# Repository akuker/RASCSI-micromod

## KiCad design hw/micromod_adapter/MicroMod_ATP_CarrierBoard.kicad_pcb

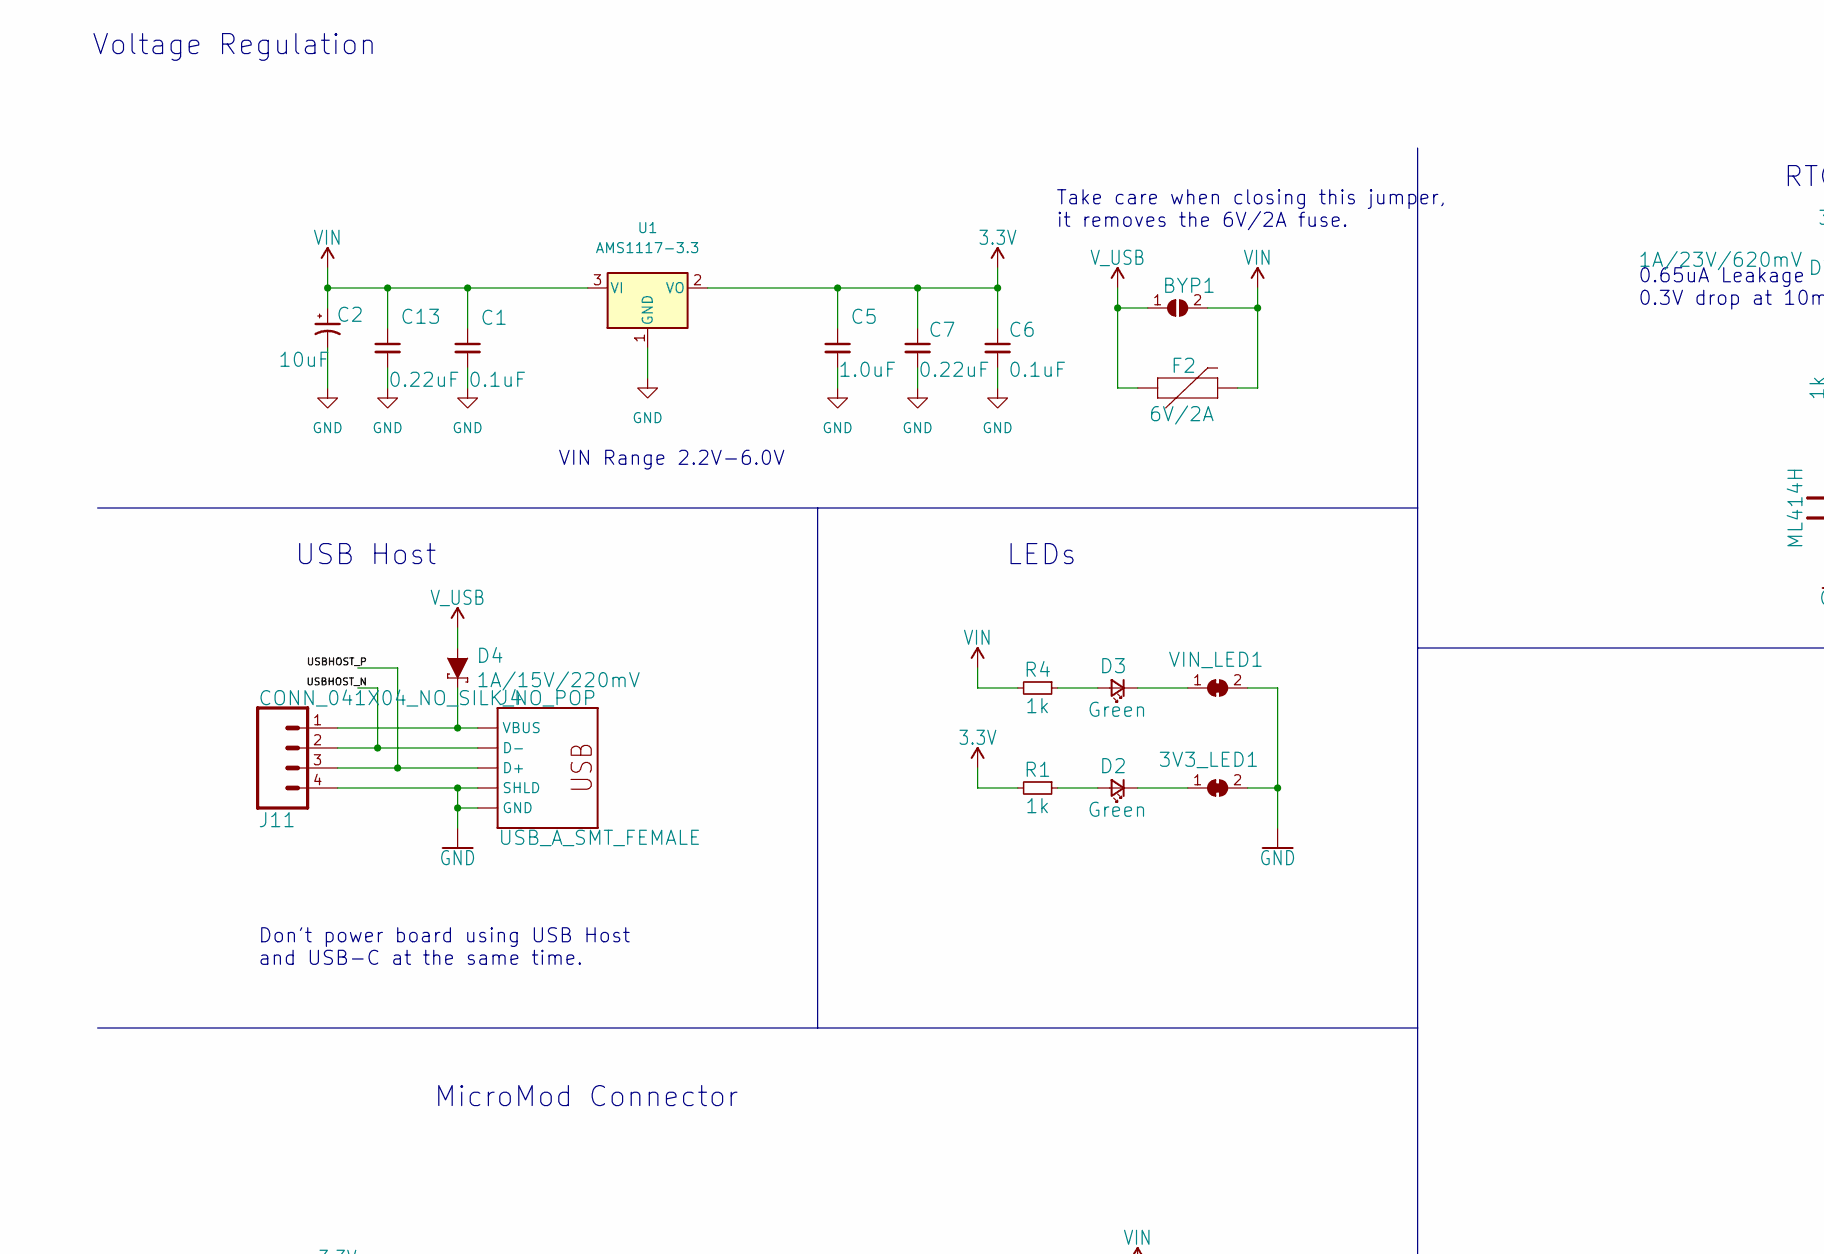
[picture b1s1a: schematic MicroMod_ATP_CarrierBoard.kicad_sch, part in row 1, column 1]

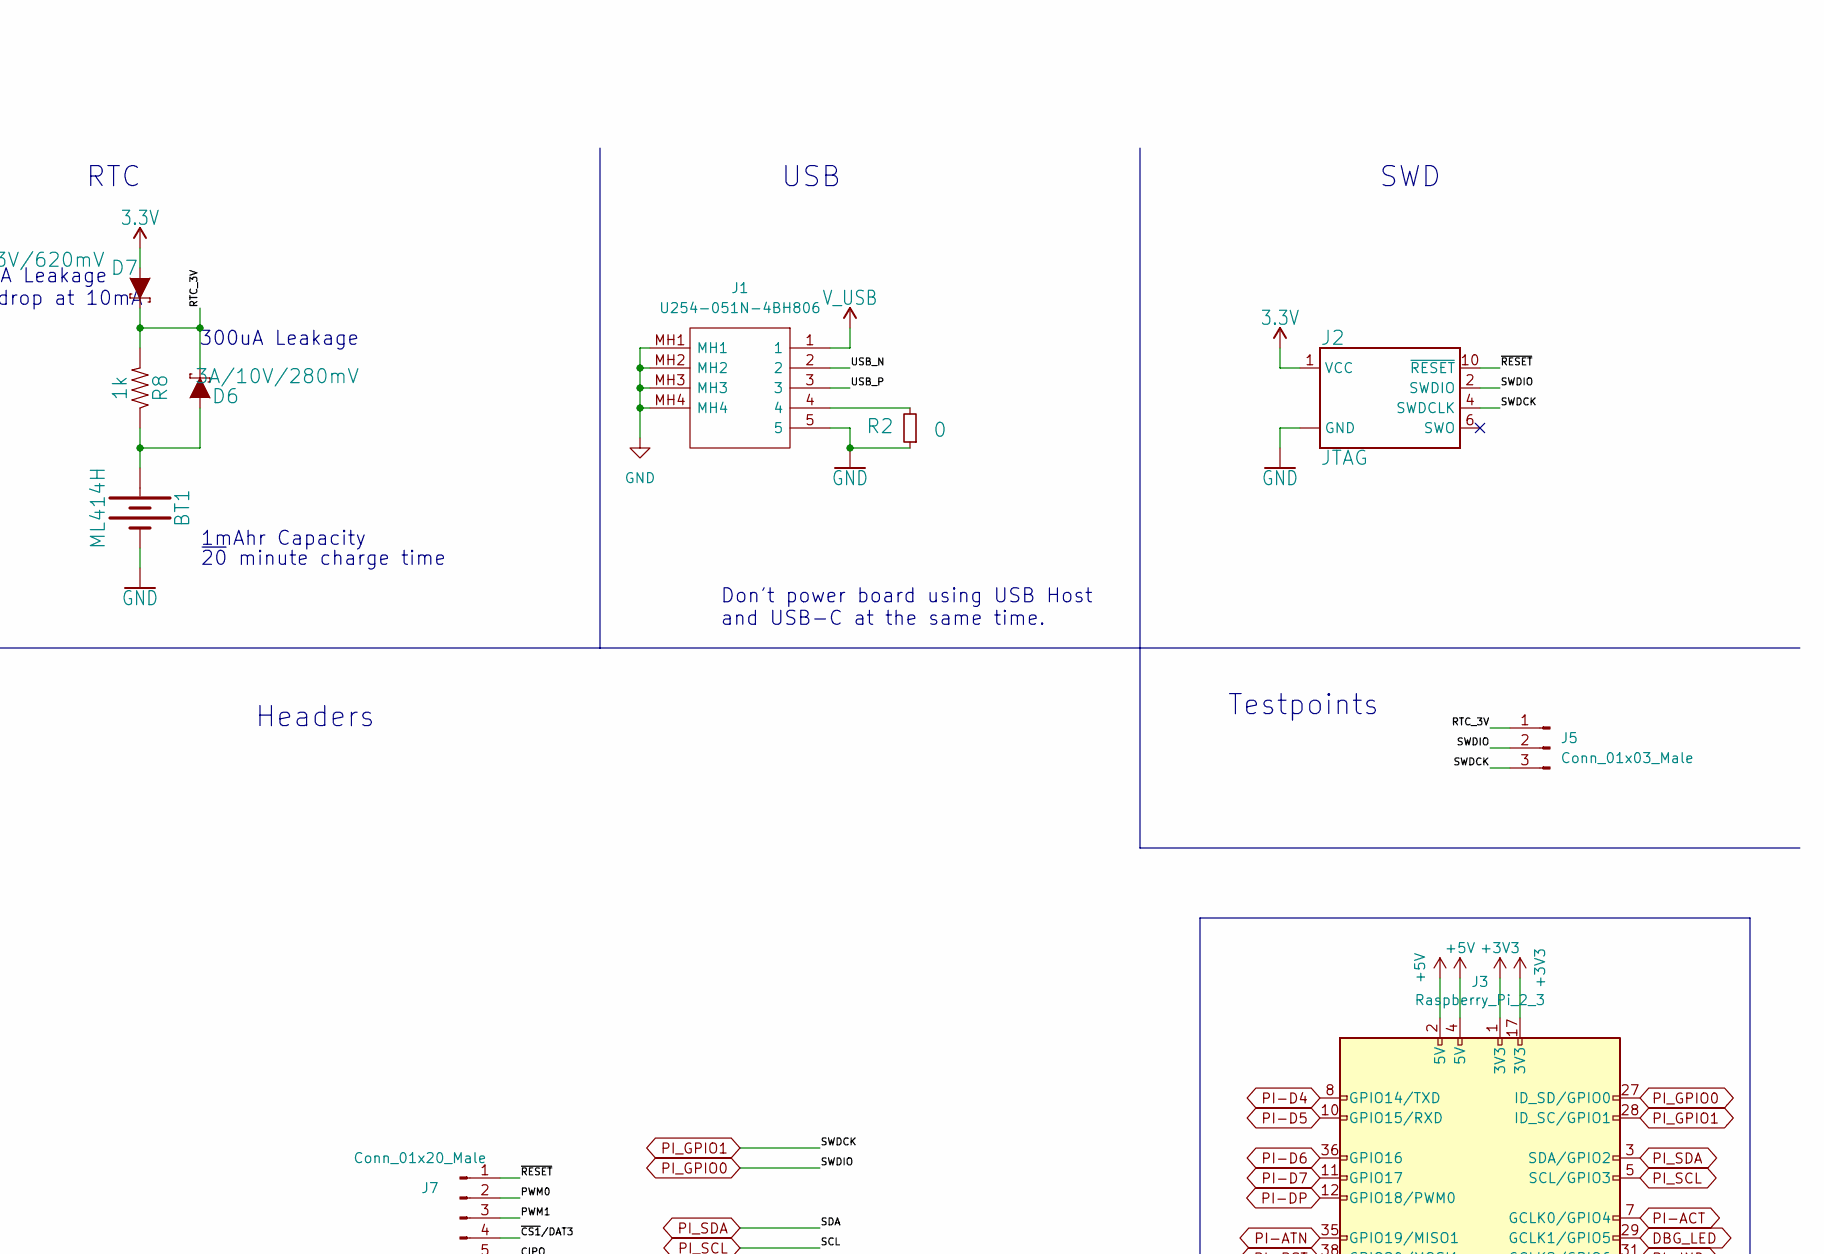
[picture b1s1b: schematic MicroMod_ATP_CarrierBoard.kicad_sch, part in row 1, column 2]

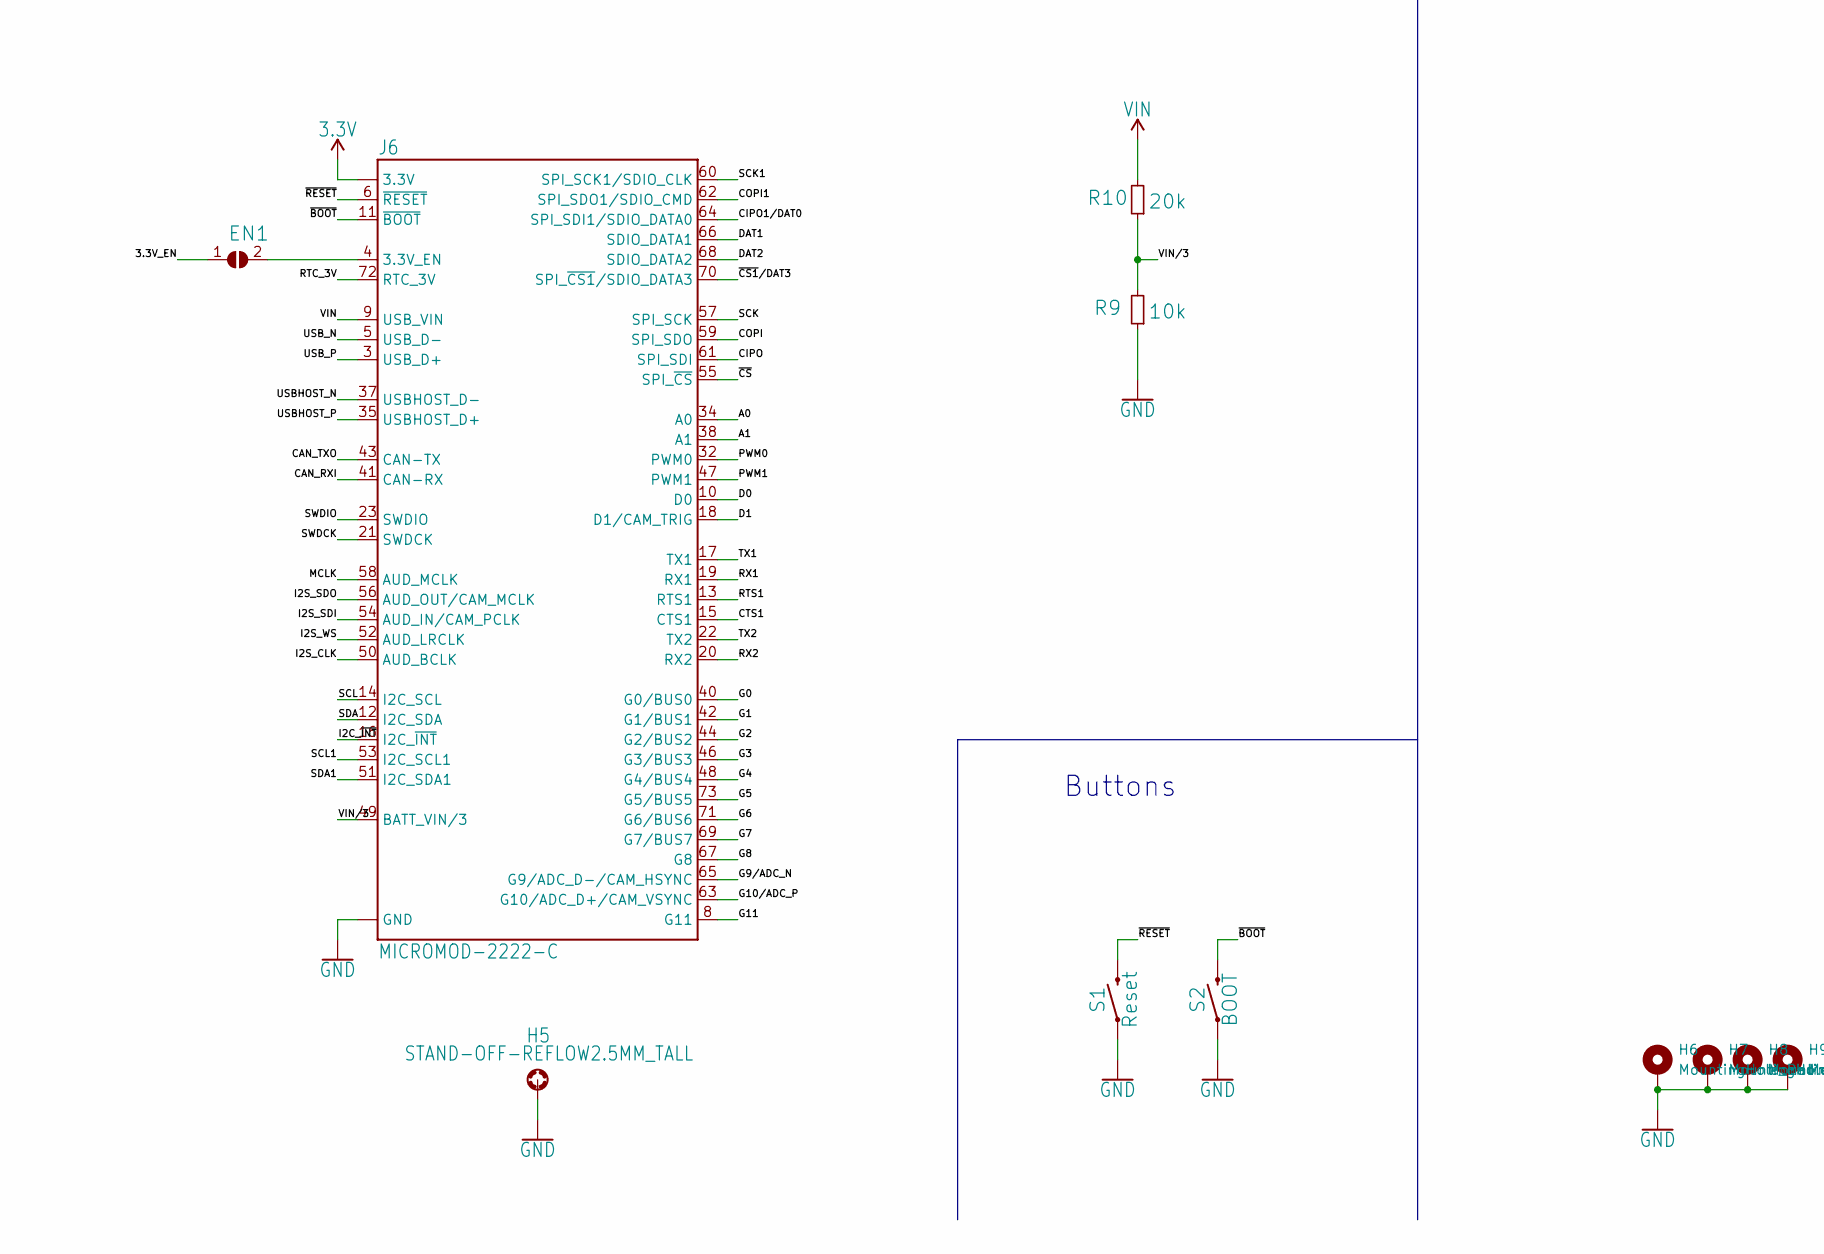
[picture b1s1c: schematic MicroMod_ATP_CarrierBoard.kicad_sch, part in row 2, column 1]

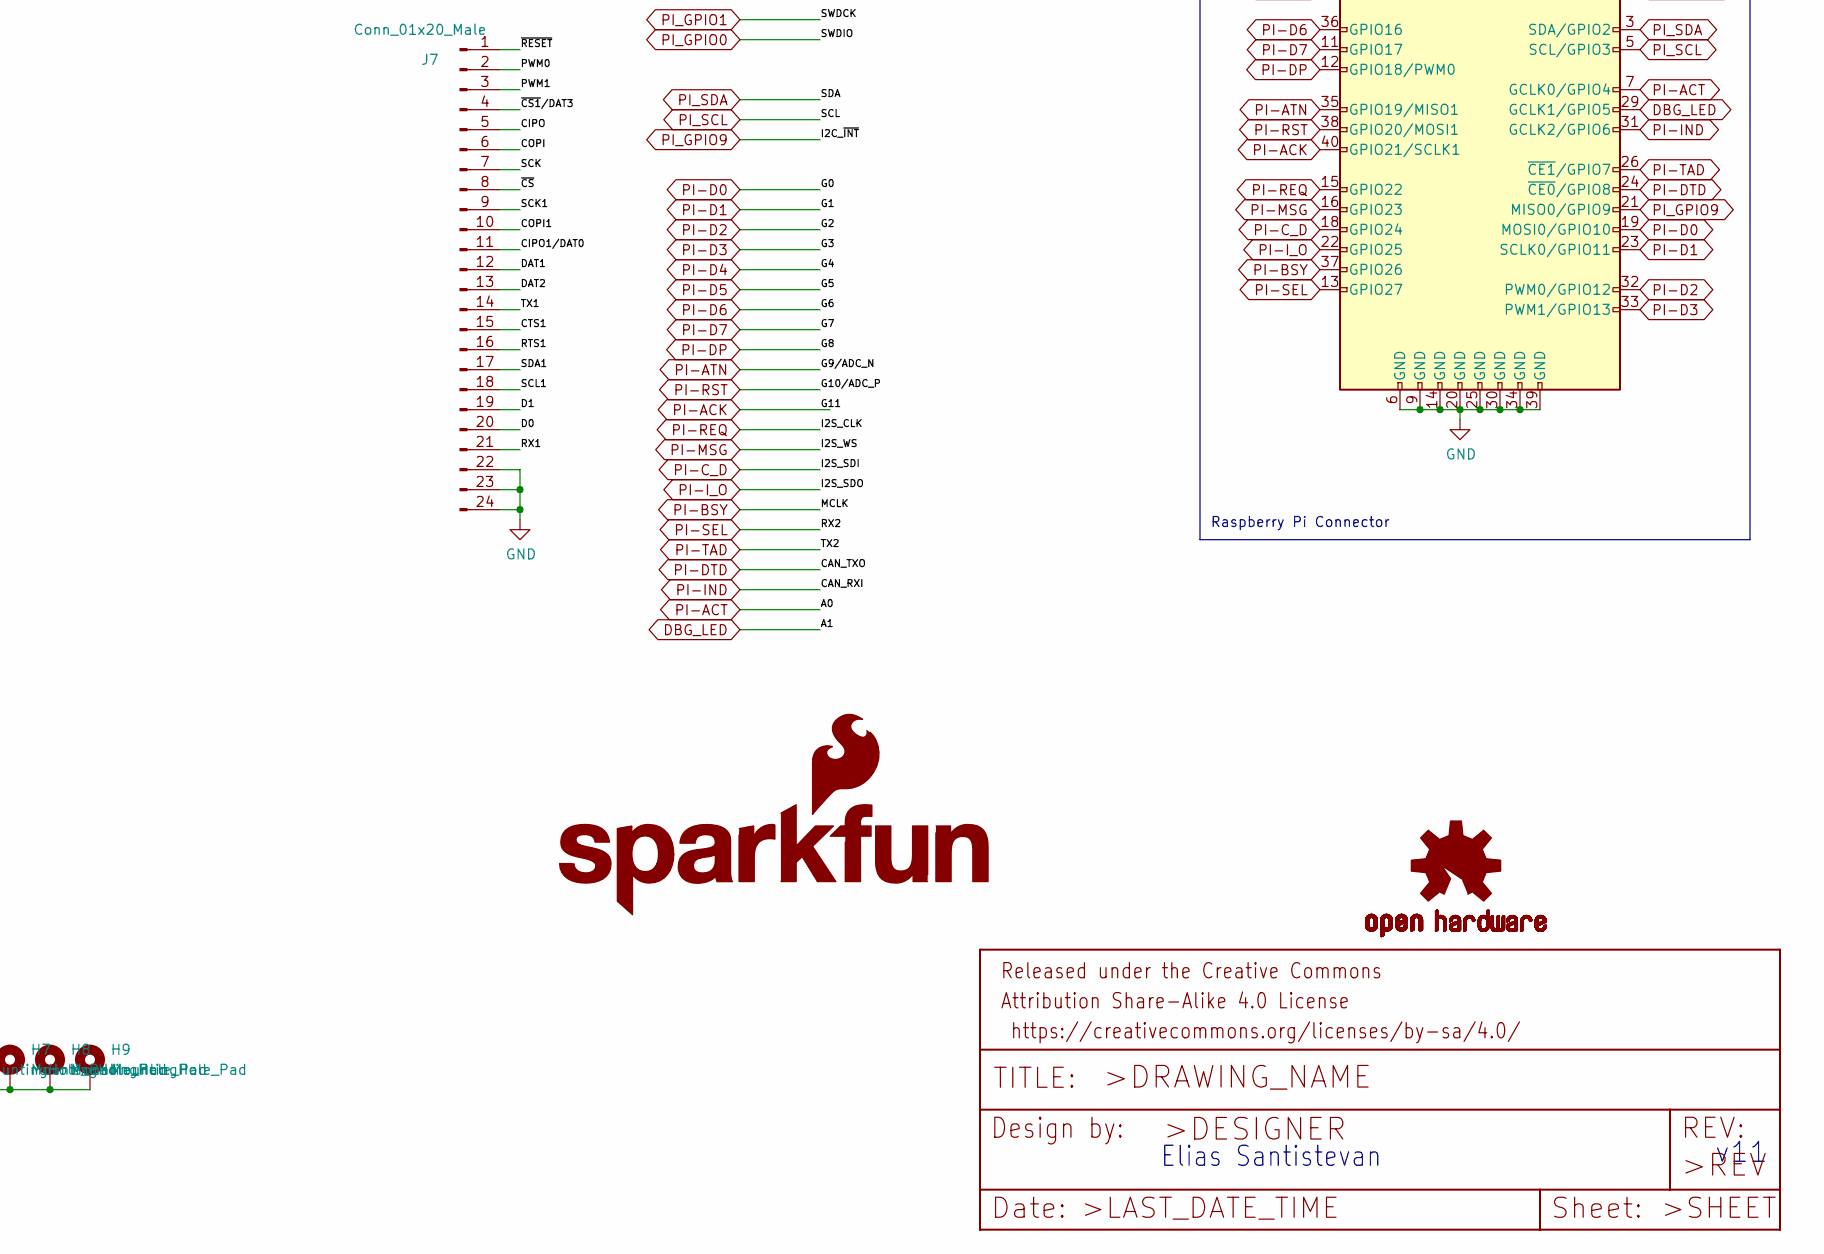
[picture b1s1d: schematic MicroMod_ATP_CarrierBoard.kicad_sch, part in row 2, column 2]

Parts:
3V3_LED1: JUMPER-SMT_2_NC_TRACE_SILK; SolderJumper-2_P1.3mm_Bridged_RoundedPad1.0x1.5mm
BT1: ML414H; ML414H_IV01E
BYP1: JUMPER-SMT_2_NO_SILK; SolderJumper-2_P1.3mm_Open_RoundedPad1.0x1.5mm
C1, C6: 0.1uF; C_0805_2012Metric_Pad1.18x1.45mm_HandSolder; LCSC C49678
C2: 10uF; C_1206_3216Metric_Pad1.33x1.80mm_HandSolder; LCSC C7171
C5: 1.0uF; C_0603_1608Metric_Pad1.08x0.95mm_HandSolder; LCSC C15849
C7, C13: 0.22uF; C_0805_2012Metric_Pad1.18x1.45mm_HandSolder; LCSC C5378
D2, D3: Green; LED_0805_2012Metric_Pad1.15x1.40mm_HandSolder; LCSC C2297
D4: 1A/15V/220mV; DO-214BA
D6: 3A/10V/280mV; SOD-323
D7: 1A/23V/620mV; SOD-323
EN1: JUMPER-SMT_2_NO_SILK; SolderJumper-2_P1.3mm_Open_RoundedPad1.0x1.5mm
F2: 6V/2A; 1210
FRAME1: FRAME-LEDGER; CREATIVE_COMMONS
H5: STAND-OFF-REFLOW2.5MM_TALL; STAND-OFF-REFLOW-M2.5
H6, H7, H8, H9: MountingHole_Pad; MountingHole_2.7mm_M2.5_Pad_Via
J1: U254-051N-4BH806; U254051N4BH806; Manufacturer_Part_Number U254-051N-4BH806
J2: JTAG; 2X5-PTH-1.27MM
J3: Raspberry_Pi_2_3; PinSocket_2x20_P2.54mm_Vertical; Manufacturer_Part_Number C50982; LCSC C50982
J4: USB_A_SMT_FEMALE; USB-A-S-SILK-FEMALE
J5: Conn_01x03_Male; PinHeader_1x03_P2.54mm_Vertical
J6: MICROMOD-2222-C; M.2-CONNECTOR-E
J7: Conn_01x20_Male; PinHeader_1x24_P1.00mm_Vertical
J11: CONN_041X04_NO_SILK_NO_POP; 1X04_NO_SILK
LOGO1: SFE_LOGO_NAME_FLAME.1_INCH; SFE_LOGO_NAME_FLAME_.1
LOGO3: OSHW-LOGOMINI; OSHW-LOGO-MINI
R1, R4: 1k; C_0805_2012Metric_Pad1.18x1.45mm_HandSolder; LCSC C17737
R2: 0; R_0805_2012Metric_Pad1.20x1.40mm_HandSolder; lcsc C17477
R8: 1k; 0603
R9: 10k; R_0805_2012Metric_Pad1.20x1.40mm_HandSolder; LCSC C17414
R10: 20k; R_0805_2012Metric_Pad1.20x1.40mm_HandSolder
S1: Reset; SW_PUSH_6mm
S2: BOOT; SW_PUSH_6mm
U1: AMS1117-3.3; SOT-223-3_TabPin2; LCSC C6186
VIN_LED1: JUMPER-SMT_2_NC_TRACE_SILK; SolderJumper-2_P1.3mm_Bridged_RoundedPad1.0x1.5mm

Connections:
3.3V: C5.1, C6.1, C7.1, D7.A, J2.1 (VCC), J6.2 (3.3V), J6.74 (3.3V), R1.2, U1.2 (VO)
+3V3: J3.1 (3V3), J3.17 (3V3)
+5V: J3.2 (5V), J3.4 (5V)
/3.3V_EN: EN1.1 (A)
/CIPO: J6.61 (SPI_SDI), J7.5
/CIPO1/DAT0: J6.64 (SPI_SDI1/SDIO_DATA0), J7.11
/COPI: J6.59 (SPI_SDO), J7.6
/COPI1: J6.62 (SPI_SDO1/SDIO_CMD), J7.10
/CTS1: J6.15 (CTS1), J7.15
/D0: J6.10 (D0), J7.20
/D1: J6.18 (D1/CAM_TRIG), J7.19
/DAT1: J6.66 (SDIO_DATA1), J7.12
/DAT2: J6.68 (SDIO_DATA2), J7.13
/PWM0: J6.32 (PWM0), J7.2
/PWM1: J6.47 (PWM1), J7.3
/RTC_3V: D6.C, D7.C, J5.1, J6.72 (RTC_3V), R8.2
/RTS1: J6.13 (RTS1), J7.16
/RX1: J6.19 (RX1), J7.21
/SCK: J6.57 (SPI_SCK), J7.7
/SCK1: J6.60 (SPI_SCK1/SDIO_CLK), J7.9
/SCL1: J6.53 (I2C_SCL1), J7.18
/SDA1: J6.51 (I2C_SDA1), J7.17
/TX1: J6.17 (TX1), J7.14
/USBHOST_N: J4.D-, J6.37 (USBHOST_D-), J11.2
/USBHOST_P: J4.D+, J6.35 (USBHOST_D+), J11.3
/USB_N: J1.2, J6.5 (USB_D-)
/USB_P: J1.3, J6.3 (USB_D+)
/VIN/3: J6.49 (BATT_VIN/3), R9.2, R10.1
/~BOOT: J6.11 (~BOOT), S2.3 (2), S2.4 (2)
/~CS1/DAT3: J6.70 (SPI_~CS1/SDIO_DATA3), J7.4
/~CS: J6.55 (SPI_~CS), J7.8
/~RESET: J2.10 (~RESET), J6.6 (~RESET), J7.1, S1.3 (2), S1.4 (2)
DBG_LED: J3.29 (GCLK1/GPIO5), J6.38 (A1)
GND: 3V3_LED1.2 (B), BT1.-, C1.2, C2.2, C5.2, C6.2, C7.2, C13.2, H5.1, H6.1, H7.1, H8.1, H9.1, J1.5, J1.MH1, J1.MH2, J1.MH3, J1.MH4, J2.3 (GND), J2.5 (GND), J2.9 (GND), J3.6 (GND), J3.9 (GND), J3.14 (GND), J3.20 (GND), J3.25 (GND), J3.30 (GND), J3.34 (GND), J3.39 (GND), J4.GND, J4.SHLD1 (SHLD), J4.SHLD2 (SHLD), J6.1 (GND), J6.7 (GND), J6.33 (GND), J6.36 (GND), J6.39 (GND), J6.45 (GND), J6.75 (GND), J7.22, J7.23, J7.24, J11.4, R2.1, R9.1, S1.1, S1.2 (1), S2.1, S2.2 (1), U1.1 (GND), VIN_LED1.2 (B)
unnamed: 3V3_LED1.1 (A), D2.1 (K)
unnamed: BT1.+, D6.A, R8.1
unnamed: D3.2 (A), R4.1
unnamed: D4.C, J4.VBUS, J11.1
unnamed: J1.4, R2.2
unnamed: EN1.2 (B), J6.4 (3.3V_EN)
unnamed: D2.2 (A), R1.1
unnamed: D3.1 (K), VIN_LED1.1 (A)
PI-ACK: J3.40 (GPIO21/SCLK1), J6.8 (G11)
PI-ACT: J3.7 (GCLK0/GPIO4), J6.34 (A0)
PI-ATN: J3.35 (GPIO19/MISO1), J6.65 (G9/ADC_D-/CAM_HSYNC)
PI-BSY: J3.37 (GPIO26), J6.58 (AUD_MCLK)
PI-C_D: J3.18 (GPIO24), J6.54 (AUD_IN/CAM_PCLK)
PI-D0: J3.19 (MOSI0/GPIO10), J6.40 (G0/BUS0)
PI-D1: J3.23 (SCLK0/GPIO11), J6.42 (G1/BUS1)
PI-D2: J3.32 (PWM0/GPIO12), J6.44 (G2/BUS2)
PI-D3: J3.33 (PWM1/GPIO13), J6.46 (G3/BUS3)
PI-D4: J3.8 (GPIO14/TXD), J6.48 (G4/BUS4)
PI-D5: J3.10 (GPIO15/RXD), J6.73 (G5/BUS5)
PI-D6: J3.36 (GPIO16), J6.71 (G6/BUS6)
PI-D7: J3.11 (GPIO17), J6.69 (G7/BUS7)
PI-DP: J3.12 (GPIO18/PWM0), J6.67 (G8)
PI-DTD: J3.24 (~CE0/GPIO8), J6.43 (CAN-TX)
PI-IND: J3.31 (GCLK2/GPIO6), J6.41 (CAN-RX)
PI-I_O: J3.22 (GPIO25), J6.56 (AUD_OUT/CAM_MCLK)
PI-MSG: J3.16 (GPIO23), J6.52 (AUD_LRCLK)
PI-REQ: J3.15 (GPIO22), J6.50 (AUD_BCLK)
PI-RST: J3.38 (GPIO20/MOSI1), J6.63 (G10/ADC_D+/CAM_VSYNC)
PI-SEL: J3.13 (GPIO27), J6.20 (RX2)
PI-TAD: J3.26 (~CE1/GPIO7), J6.22 (TX2)
PI_GPIO0: J2.2 (SWDIO), J3.27 (ID_SD/GPIO0), J5.2, J6.23 (SWDIO)
PI_GPIO1: J2.4 (SWDCLK), J3.28 (ID_SC/GPIO1), J5.3, J6.21 (SWDCK)
PI_GPIO9: J3.21 (MISO0/GPIO9), J6.16 (I2C_~INT)
PI_SCL: J3.5 (SCL/GPIO3), J6.14 (I2C_SCL)
PI_SDA: J3.3 (SDA/GPIO2), J6.12 (I2C_SDA)
VIN: BYP1.2 (B), C1.1, C2.1, C13.1, F2.2, J6.9 (USB_VIN), R4.2, R10.2, U1.3 (VI)
V_USB: BYP1.1 (A), D4.A, F2.1, J1.1

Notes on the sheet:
Voltage Regulation
Don't power board using USB Host and USB-C at the same time.
1mAhr Capacity
USB Host
Elias Santistevan
Raspberry Pi Connector
300uA Leakage
~{20} minute charge time
0.65uA Leakage 0.3V drop at 10mA
USB
SWD
Take care when closing this jumper, it removes the 6V/2A fuse.
MicroMod Connector
v11
LEDs
Headers
RTC
Testpoints
Buttons
VIN Range 2.2V-6.0V

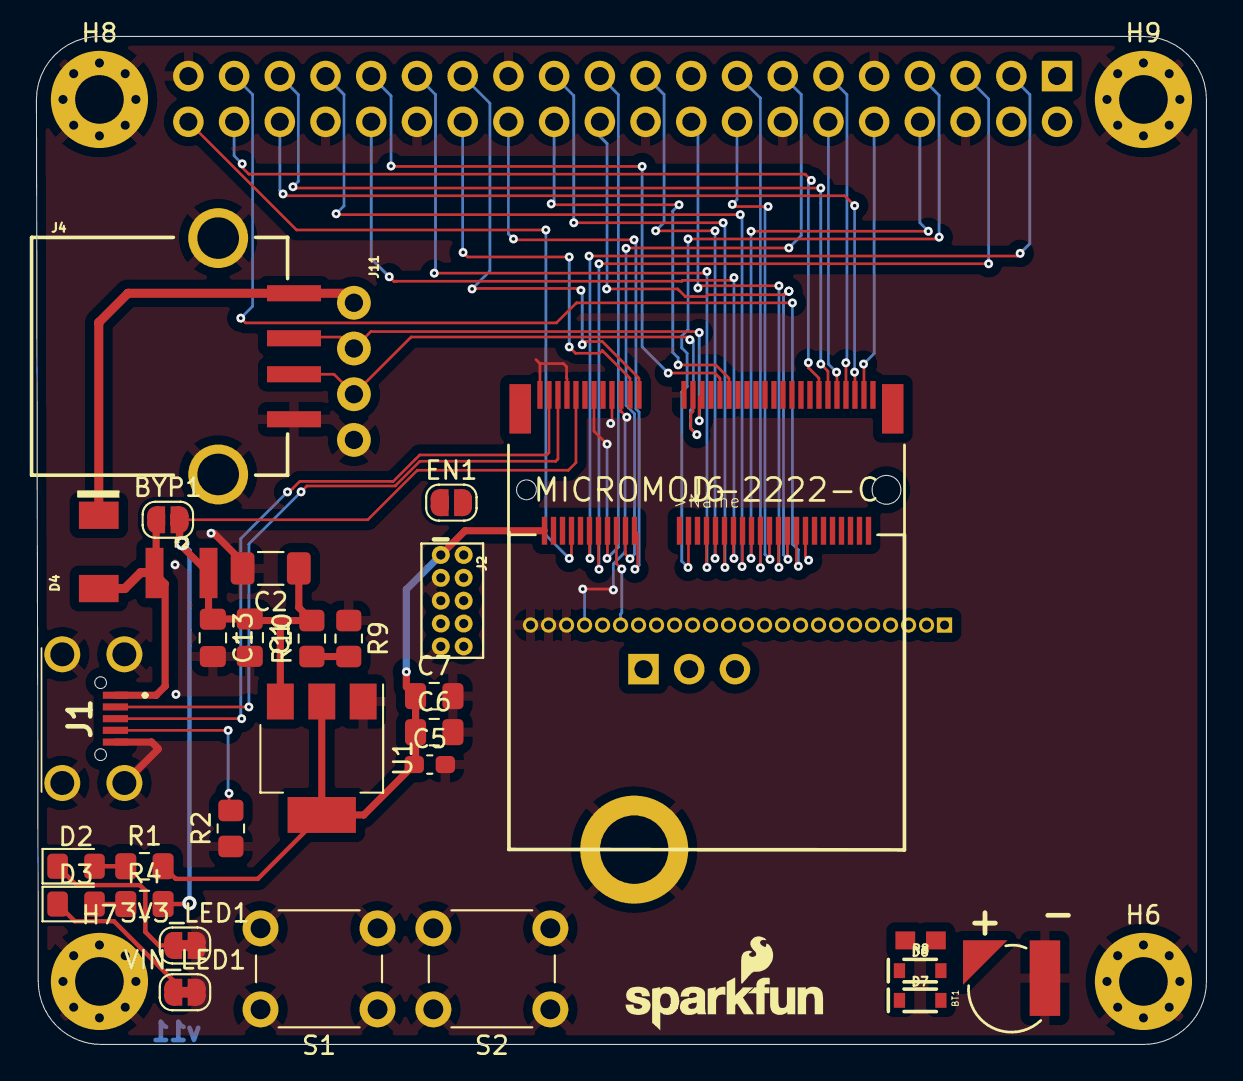
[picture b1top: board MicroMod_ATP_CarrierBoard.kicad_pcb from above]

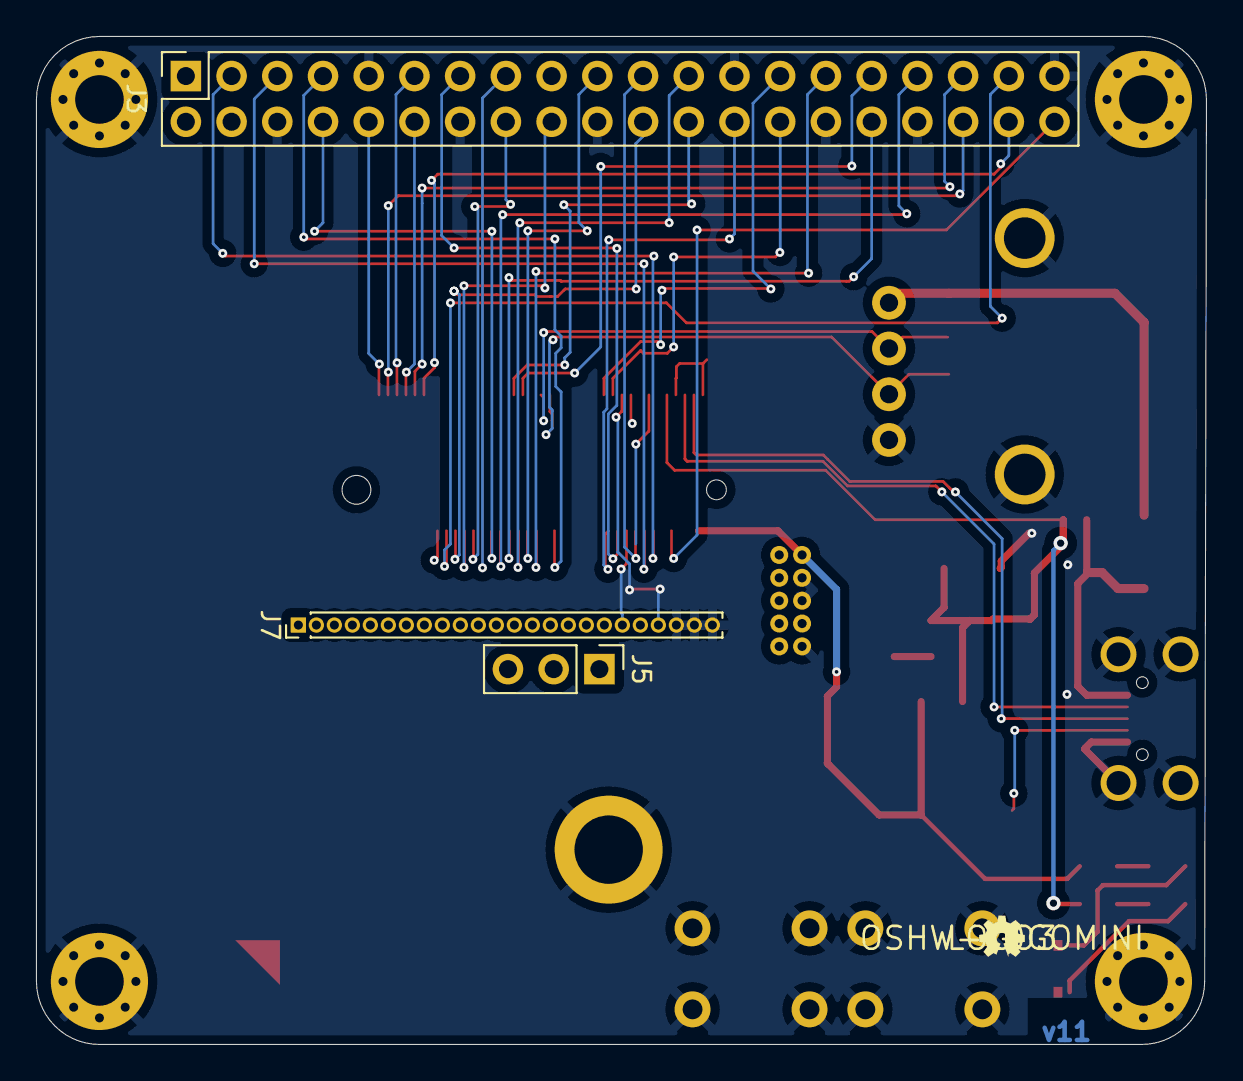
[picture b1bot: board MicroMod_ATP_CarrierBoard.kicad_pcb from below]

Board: 2 copper layers, 65.0 x 56.0 mm, 42 parts (4 on the bottom side), 69 nets.

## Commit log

2022-02-02 Convert Sparkfun carrierboard to kicad
2022-02-02 did some stuff
2022-02-06 more routing

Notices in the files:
hw/micromod_adapter/MicroMod_ATP_CarrierBoard.kicad_sch:
https://creativecommons.org/licenses/by-sa/4.0
Released under the Creative Commons
parts and their libraries:
Released under the Creative Commons Attribution Share-Alike 4.0 License
